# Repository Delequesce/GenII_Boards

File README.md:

## Rev 3 Changes

### Pi Interface and Power Board
1) ~~Set 4 LSBs of each color going into the RGB interface HIGH. This still allows for 4096 possible colors but frees up 12 total GPIOs.~~
2) ~~Replaced source switching circuitry with a source selector IC (LTC4412)~~. ~~Also implemented circuitry to enable the STM32 to shutdown and wakeup the Pi with the power button for better power management.~~ 
3) ~~Replaced the Pi Zero W with a Pi Zero 2 W.~~
4) ~~Added I2C RESET pin for enabling the capacitive touch screen~~
5) ~~Moved the FPC connector to the Measurement Board to the top of the board to ease assembly.~~ 
6) ~~Moved the RGB and I2C connectors to the screen closer to the edge (or top with flipped connections) to ease assembly.~~ 
7) ~~Fixed wiring issues for Vdd and Vcc out to the Measurement Board.~~
8) ~~Increased the size of the mounting holes for the battery cables to ease connection. (0.65 mm diameter for 22 AWG)~~
9) ~~Generally improved power routing~~
10) ~~Improved PWM backlight enable routing for better fidelity.~~
11) ~~Specced out smaller battery connectors to ease assembly and reduce size. (22 AWG, Amazon)~~
12) ~~Moved the Vdd Main LDO to the Measurement Board~~
13) ~~Added a fuse to the TPS2400 circuit and also a fuse after the source selector.~~
14) ~~Added a small board meant to be separated for interfacing the pushbutton reset switch with the rest of the circuit.~~

### Measurement Board
1) ~~Fixed PWM Heater signal routing~~ 
2) ~~Flipped FPC connector to Pi Board to top of board to ease assembly. Checked wiring against the Pi board.~~
3) ~~Moved Vdd Main LDO from Pi Board.~~ 
4) ~~Added external interrupt pin and Vcc controller output pin to interface with external pushbutton board. Needed to add 50 mils (1.27 mm) to board length.~~
5) ~~Changed the ADR4530 to the MAX6070, a cheaper buffered reference requiring fewer parts.~~

### Heater Board
1) ~~Reduced the size of vias and made more of them for better heating and lower losses. ~~
2) Moved the thermistors slightly farther from the center to improve temperature tracking. Alternately just reduced the size of the heating area to improve tracking without separating the thermistors from the chip. (Maybe)

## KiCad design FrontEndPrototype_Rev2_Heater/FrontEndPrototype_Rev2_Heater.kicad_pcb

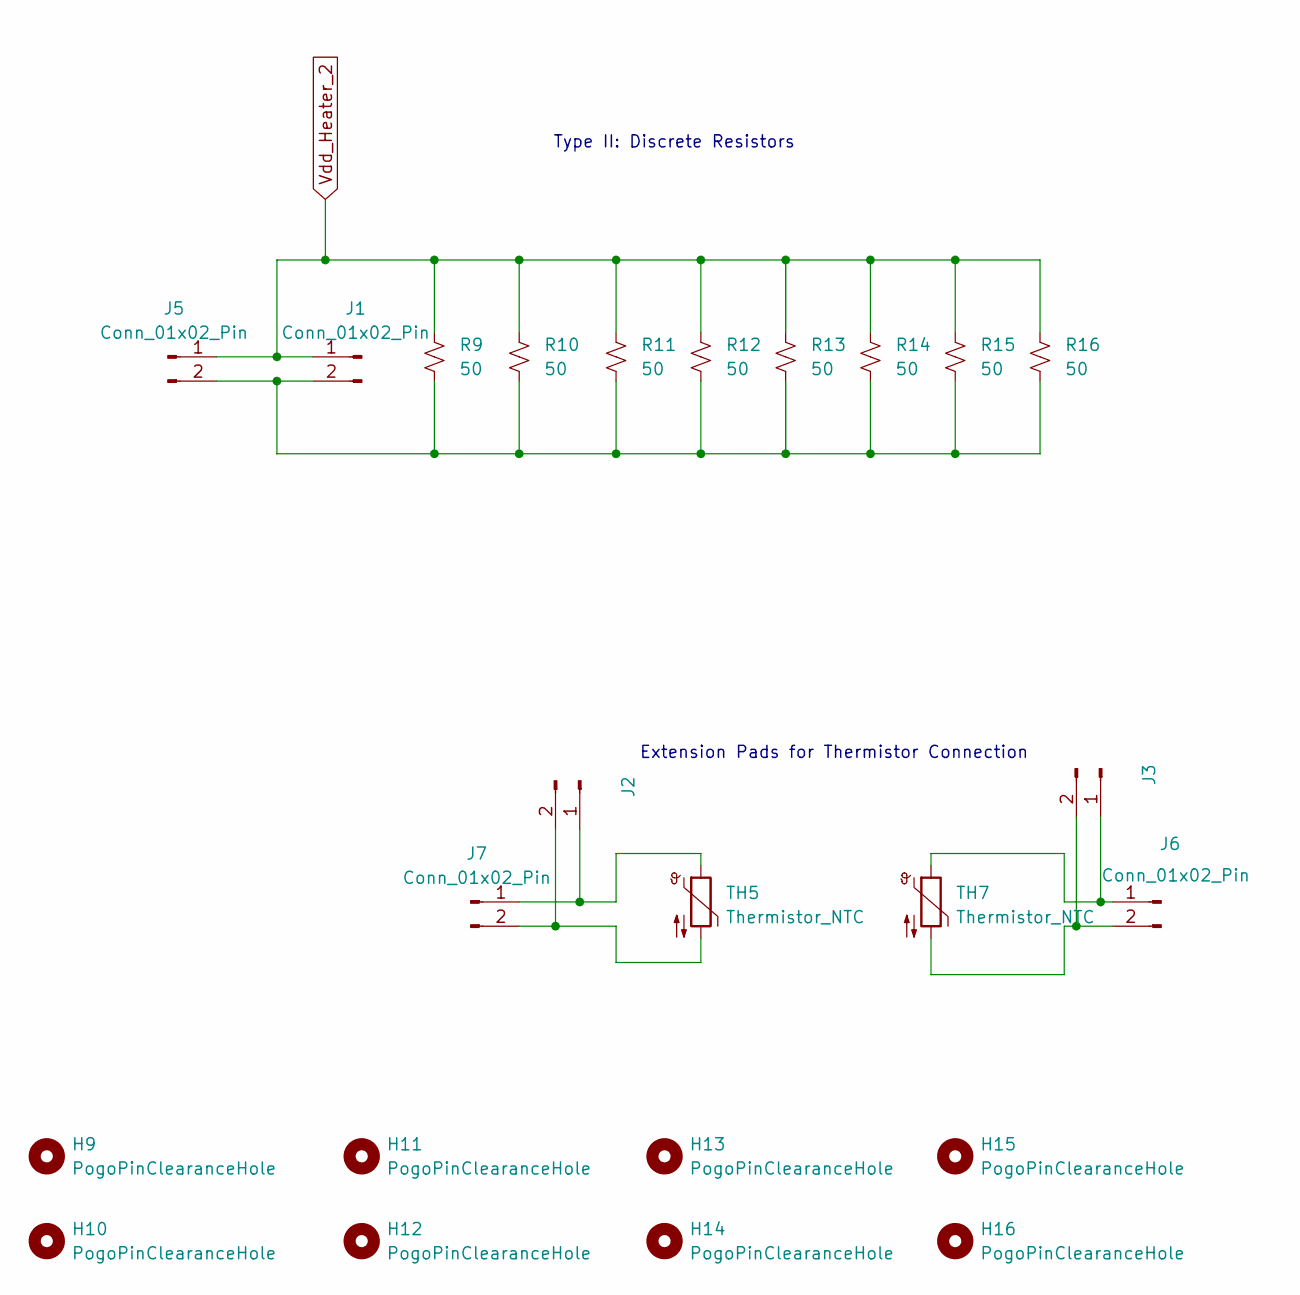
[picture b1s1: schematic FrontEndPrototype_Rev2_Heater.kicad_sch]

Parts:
H9, H10, H11, H12, H13, H14, H15, H16: PogoPinClearanceHole; PogoClearanceHole
J1, J5, J6, J7: Conn_01x02_Pin; Samtec_Pin_Socket_SS_102_G_2
J2, J3: Conn_01x02_Pin; Thermistor_ExtensionPad
R9, R10, R11, R12, R13, R14, R15, R16: 50; R_2010_5025Metric_Pad1.40x2.65mm_HandSolder
TH5, TH7: Thermistor_NTC; R_0603_1608Metric_Pad0.98x0.95mm_HandSolder

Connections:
unnamed: J1.2, J5.2, R9.1, R10.1, R11.1, R12.1, R13.1, R14.1, R15.1, R16.1
unnamed: J2.1, J7.1, TH5.1
unnamed: J2.2, J7.2, TH5.2
unnamed: J3.1, J6.1, TH7.1
unnamed: J3.2, J6.2, TH7.2
Vdd_Heater_2: J1.1, J5.1, R9.2, R10.2, R11.2, R12.2, R13.2, R14.2, R15.2, R16.2

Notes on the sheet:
Extension Pads for Thermistor Connection
Type II: Discrete Resistors

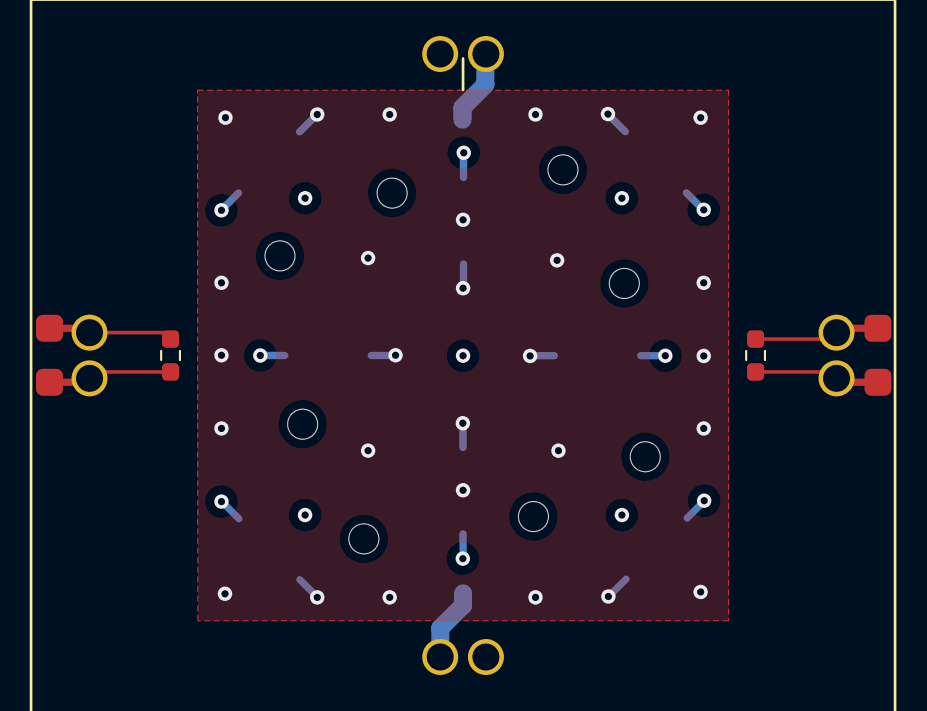
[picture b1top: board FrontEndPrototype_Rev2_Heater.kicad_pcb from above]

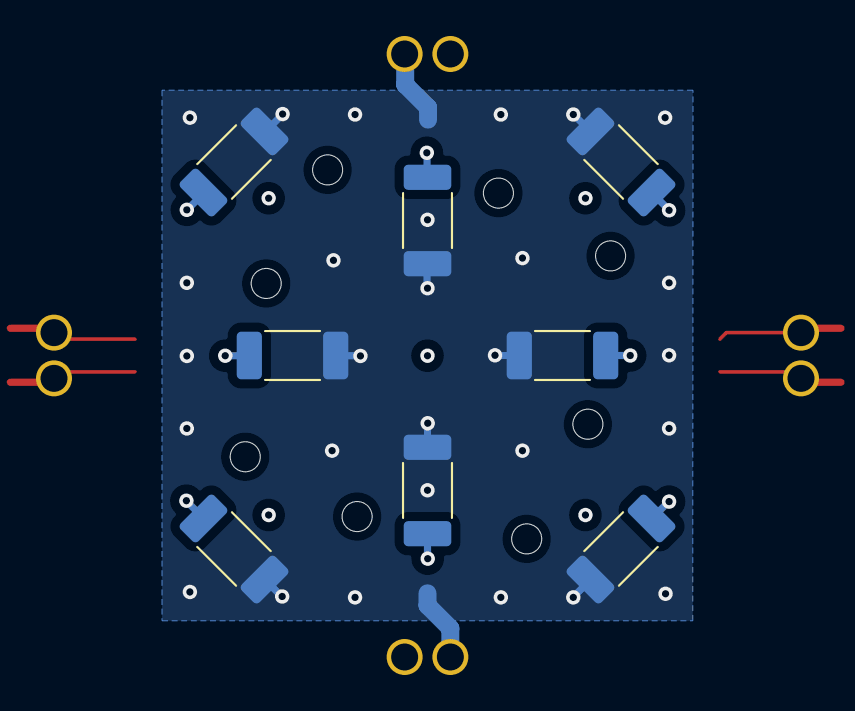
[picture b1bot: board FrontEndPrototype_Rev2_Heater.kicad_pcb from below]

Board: 4 copper layers, 24 parts (8 on the bottom side), 6 nets.

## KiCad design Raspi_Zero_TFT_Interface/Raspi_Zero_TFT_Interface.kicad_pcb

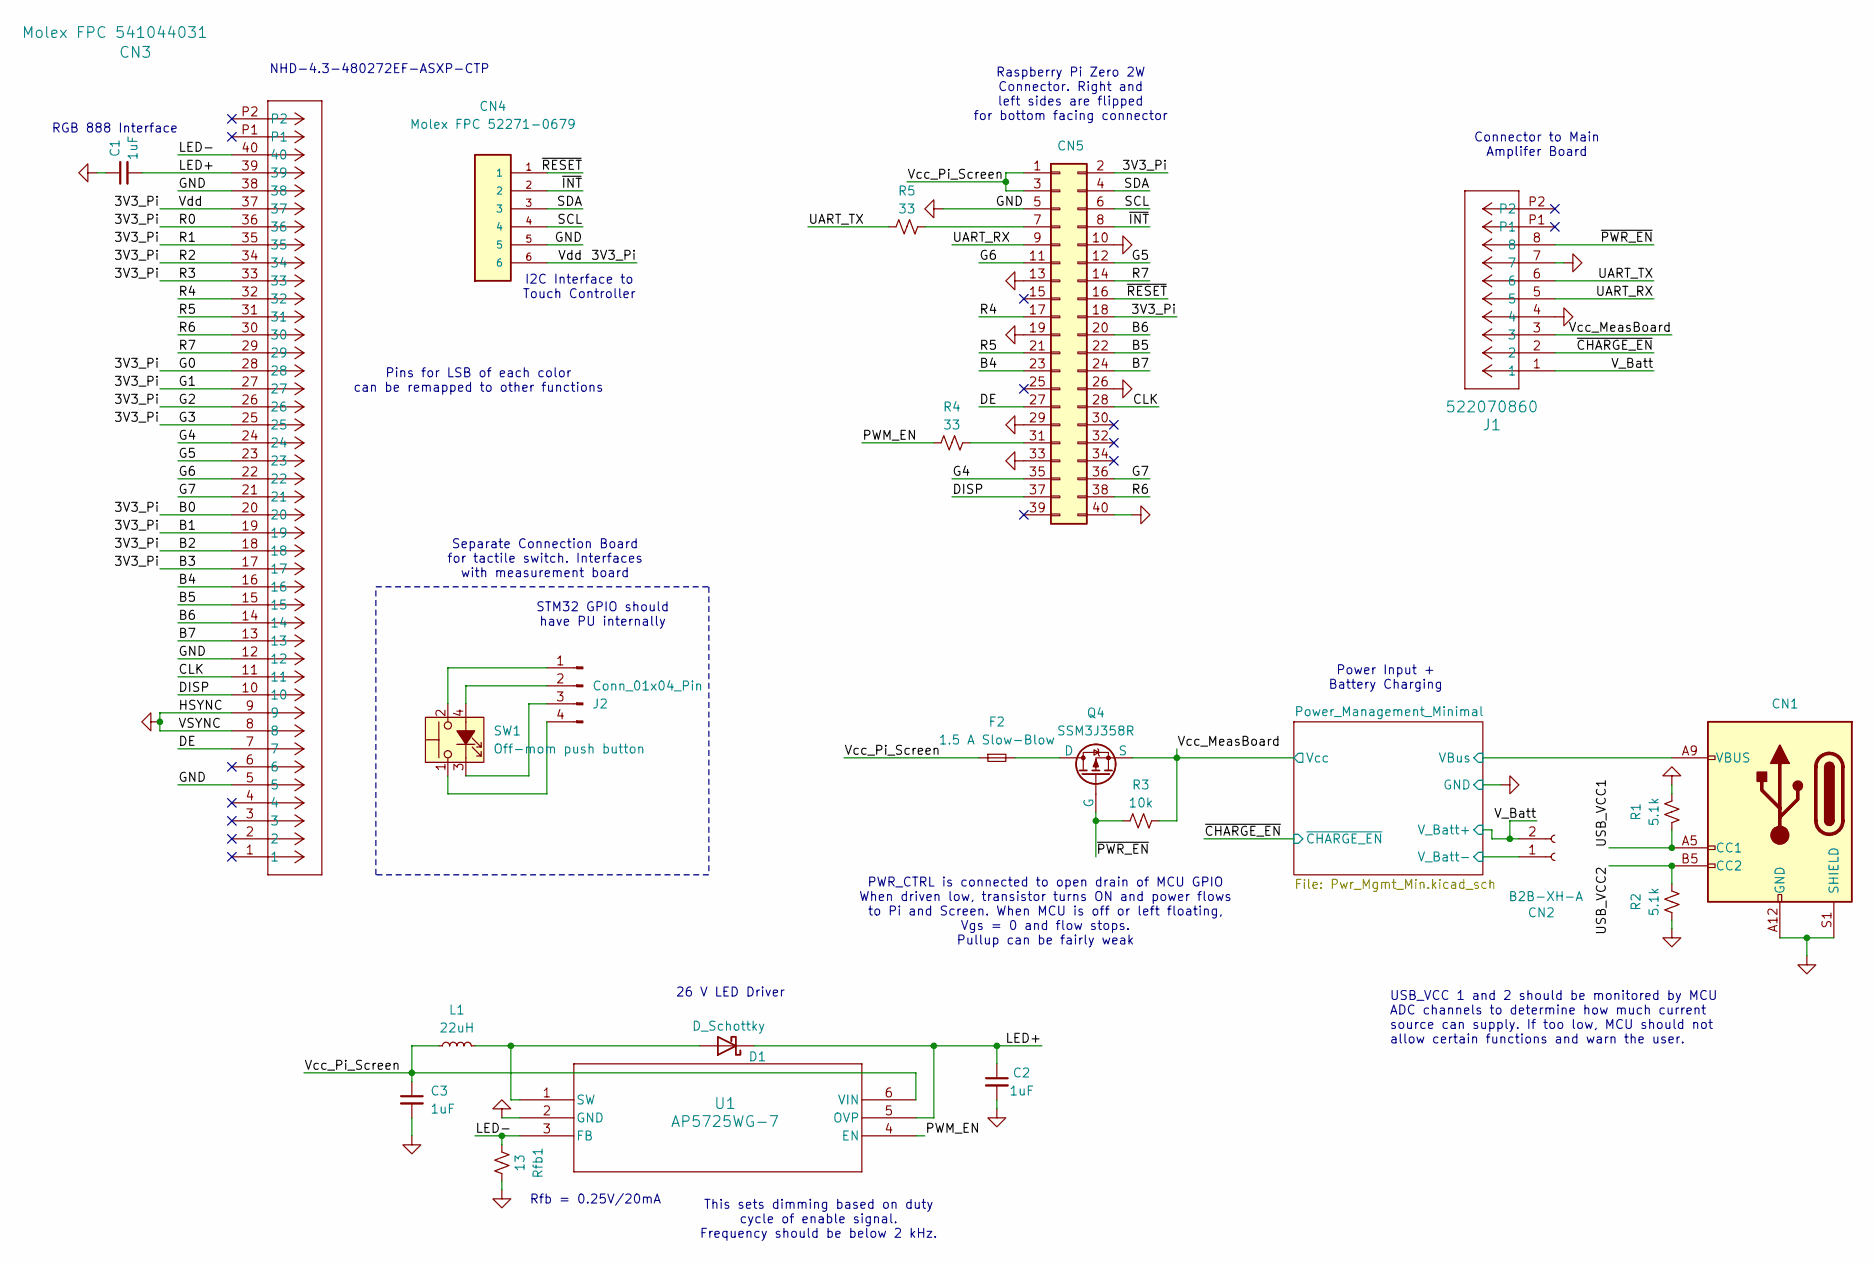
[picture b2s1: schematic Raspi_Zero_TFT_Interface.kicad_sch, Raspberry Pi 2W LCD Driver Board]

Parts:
C1, C2, C3: 1uF; C_0603_1608Metric_Pad1.08x0.95mm_HandSolder
CN1: USB_C_Receptacle_PowerOnly_6P; USB_C_Receptacle_GCT_USB4125-xx-x_6P_TopMnt_Horizontal
CN2: B2B-XH-A; JST_XH_B2B-XH-A_1x02_P2.50mm_Vertical
CN3: Molex FPC 541044031; CON_541044031_MOL
CN4: Molex FPC 52271-0679; MOLEX_52271-0679
CN5: Conn_02x20_Odd_Even; PinHeader_2x20_P2.54mm_Vertical
D1: D_Schottky; D_SOD-523
F2: 1.5 A Slow-Blow; Fuse_0603_1608Metric
J1: 522070860; CON_522070860_MOL
J2: Conn_01x04_Pin; PinHeader_1x04_P2.54mm_Vertical
L1: 22uH; L_0805_2012Metric_Pad1.15x1.40mm_HandSolder
Q4: SSM3J358R; SOT-23-3
R1, R2: 5.1k; R_0603_1608Metric_Pad0.98x0.95mm_HandSolder
R3: 10k; R_0603_1608Metric_Pad0.98x0.95mm_HandSolder
R4, R5: 33; R_0603_1608Metric_Pad0.98x0.95mm_HandSolder
Rfb1: 13; R_0603_1608Metric_Pad0.98x0.95mm_HandSolder
SW1: Off-mom push button; TL1240_LED_Switch
U1: AP5725WG-7; SOT-23-6_Handsoldering

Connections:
/3V3_Pi: CN3.17, CN3.18, CN3.19, CN3.20, CN3.25, CN3.26, CN3.27, CN3.28, CN3.33, CN3.34, CN3.35, CN3.36, CN3.37, CN4.6, CN5.2, CN5.18
/B4: CN3.16, CN5.23
/B5: CN3.15, CN5.22
/B6: CN3.14, CN5.20
/B7: CN3.13, CN5.24
/CLK: CN3.11, CN5.28
/DE: CN3.7, CN5.27
/DISP: CN3.10, CN5.37
/G4: CN3.24, CN5.35
/G5: CN3.23, CN5.12
/G6: CN3.22, CN5.11
/G7: CN3.21, CN5.36
/LED+: C1.2, C2.1, CN3.39, D1.1 (K), U1.5 (OVP)
/LED-: CN3.40, Rfb1.2, U1.3 (FB)
/PWM_EN: R4.1, U1.4 (EN)
/Power_Management_Minimal/VBus: CN1.A9 (VBUS), CN1.B9 (VBUS); also elsewhere on the board
/R4: CN3.32, CN5.17
/R5: CN3.31, CN5.21
/R6: CN3.30, CN5.38
/R7: CN3.29, CN5.14
/SCL: CN4.4, CN5.6
/SDA: CN4.3, CN5.4
/UART_RX: CN5.9, J1.5
/UART_TX: J1.6, R5.1
/USB_VCC1: CN1.A5 (CC1), R1.2
/USB_VCC2: CN1.B5 (CC2), R2.2
/V_Batt: CN2.2, J1.1; also elsewhere on the board
/Vcc_MeasBoard: J1.3, Q4.2 (S), R3.2; also elsewhere on the board
/Vcc_Pi_Screen: C3.1, CN5.1, CN5.3, F2.1, L1.1, U1.6 (VIN)
/~CHARGE_EN: J1.2; also elsewhere on the board
/~INT: CN4.2, CN5.8
/~PWR_EN: J1.8, Q4.1 (G), R3.1
/~RESET: CN4.1, CN5.16
GND: C1.1, C2.2, C3.2, CN1.A12 (GND), CN1.B12 (GND), CN1.S1 (SHIELD), CN2.1, CN3.5, CN3.8, CN3.9, CN3.12, CN3.38, CN4.5, CN5.5, CN5.10, CN5.13, CN5.19, CN5.26, CN5.29, CN5.33, CN5.40, J1.4, J1.7, R1.1, R2.1, Rfb1.1, U1.2 (GND); also elsewhere on the board
unnamed: CN5.7, R5.2
unnamed: CN5.31, R4.2
unnamed: D1.2 (A), L1.2, U1.1 (SW)
unnamed: J2.1, SW1.2
unnamed: J2.2, SW1.4 (A)
unnamed: J2.3, SW1.3 (K)
unnamed: J2.4, SW1.1
unnamed: F2.2, Q4.3 (D)

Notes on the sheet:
I2C Interface to Touch Controller
RGB 888 Interface
STM32 GPIO should have PU internally
Pins for LSB of each color can be remapped to other functions
NHD-4.3-480272EF-ASXP-CTP
USB_VCC 1 and 2 should be monitored by MCU ADC channels to determine how much current source can supply. If too low, MCU should not allow certain functions and warn the user.
Separate Connection Board for tactile switch. Interfaces with measurement board
Raspberry Pi Zero 2W Connector. Right and left sides are flipped for bottom facing connector
PWR_CTRL is connected to open drain of MCU GPIO When driven low, transistor turns ON and power flows to Pi and Screen. When MCU is off or left floating, Vgs = 0 and flow stops. Pullup can be fairly weak
This sets dimming based on duty cycle of enable signal. Frequency should be below 2 kHz.
26 V LED Driver
Connector to Main Amplifer Board
Rfb = 0.25V/20mA
Power Input + Battery Charging

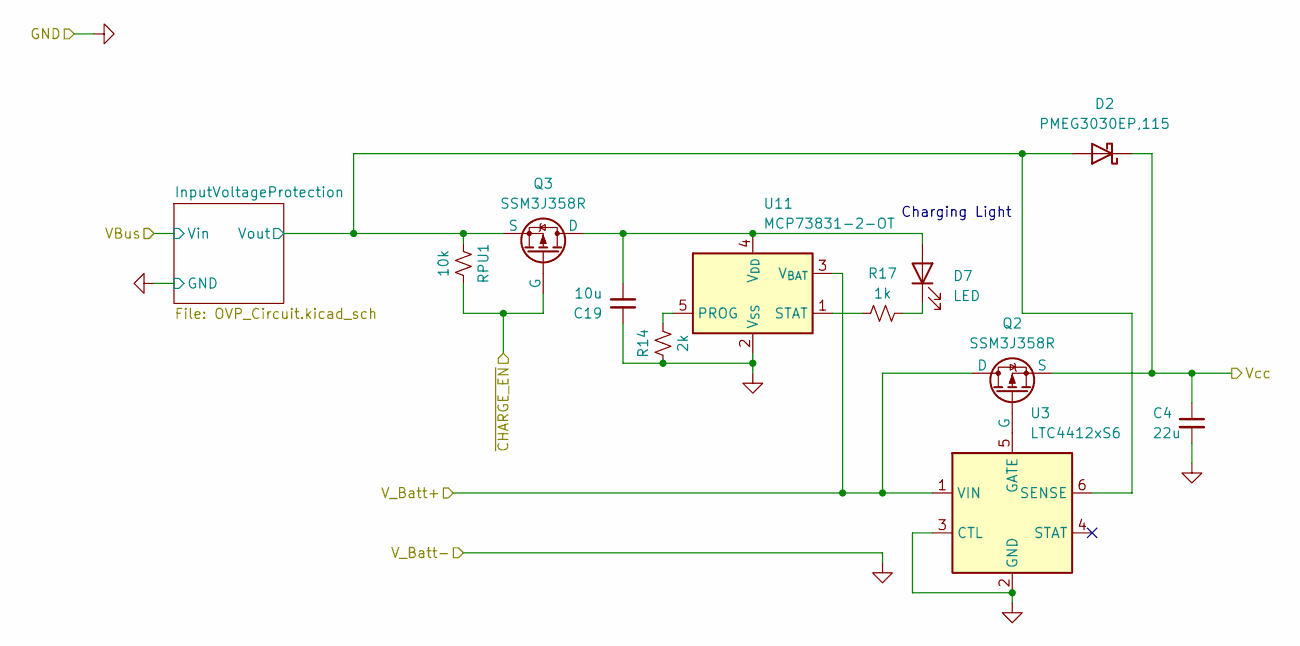
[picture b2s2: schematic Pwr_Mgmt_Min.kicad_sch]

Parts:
C4: 22u; C_0603_1608Metric_Pad1.08x0.95mm_HandSolder
C19: 10u; C_0603_1608Metric_Pad1.08x0.95mm_HandSolder
D2: PMEG3030EP,115; D_SOD-128
D7: LED; D_T-1_P2.54mm_Vertical_AnodeUp
Q2, Q3: SSM3J358R; SOT-23-3
R14: 2k; R_0603_1608Metric_Pad0.98x0.95mm_HandSolder
R17: 1k; R_0603_1608Metric_Pad0.98x0.95mm_HandSolder
RPU1: 10k; R_0603_1608Metric_Pad0.98x0.95mm_HandSolder
U3: LTC4412xS6; TSOT-23-6
U11: MCP73831-2-OT; SOT-23-5

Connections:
/Power_Management_Minimal/InputVoltageProtection/Vout: D2.2 (A), Q3.2 (S), RPU1.1, U3.6 (SENSE); also elsewhere on the board
/V_Batt: Q2.3 (D), U3.1 (VIN), U11.3 (V_{BAT}); also elsewhere on the board
/Vcc_MeasBoard: C4.1, D2.1 (K), Q2.2 (S); also elsewhere on the board
/~CHARGE_EN: Q3.1 (G), RPU1.2; also elsewhere on the board
GND: C4.2, C19.1, R14.1, U3.2 (GND), U3.3 (CTL), U11.2 (V_{SS}); also elsewhere on the board
unnamed: C19.2, D7.2 (A), Q3.3 (D), U11.4 (V_{DD})
unnamed: D7.1 (K), R17.2
unnamed: Q2.1 (G), U3.5 (GATE)
unnamed: R14.2, U11.5 (PROG)
unnamed: R17.1, U11.1 (STAT)

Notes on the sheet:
Charging Light

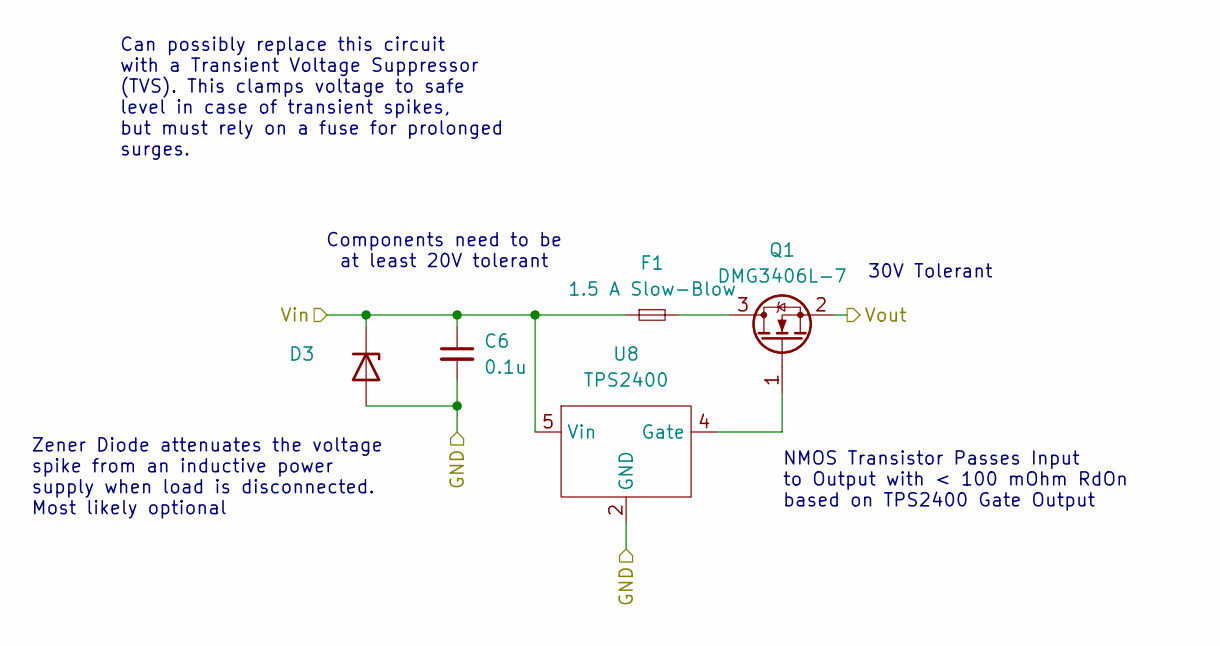
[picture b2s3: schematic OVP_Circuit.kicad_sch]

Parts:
C6: 0.1u; C_0603_1608Metric_Pad1.08x0.95mm_HandSolder
D3: NC; D_SOD-123
F1: 1.5 A Slow-Blow; Fuse_0603_1608Metric
Q1: DMG3406L-7; SOT-23-3
U8: TPS2400; SOT-23-5_HandSoldering

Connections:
/Power_Management_Minimal/InputVoltageProtection/Vout: Q1.2 (S); also elsewhere on the board
/Power_Management_Minimal/VBus: C6.1, D3.1 (K), F1.1, U8.5 (Vin); also elsewhere on the board
GND: C6.2, D3.2 (A), U8.2 (GND); also elsewhere on the board
unnamed: F1.2, Q1.3 (D)
unnamed: Q1.1 (G), U8.4 (Gate)

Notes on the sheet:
30V Tolerant
NMOS Transistor Passes Input to Output with < 100 mOhm RdOn based on TPS2400 Gate Output
Components need to be at least 20V tolerant
Zener Diode attenuates the voltage spike from an inductive power supply when load is disconnected. Most likely optional
Can possibly replace this circuit with a Transient Voltage Suppressor (TVS). This clamps voltage to safe level in case of transient spikes, but must rely on a fuse for prolonged surges.

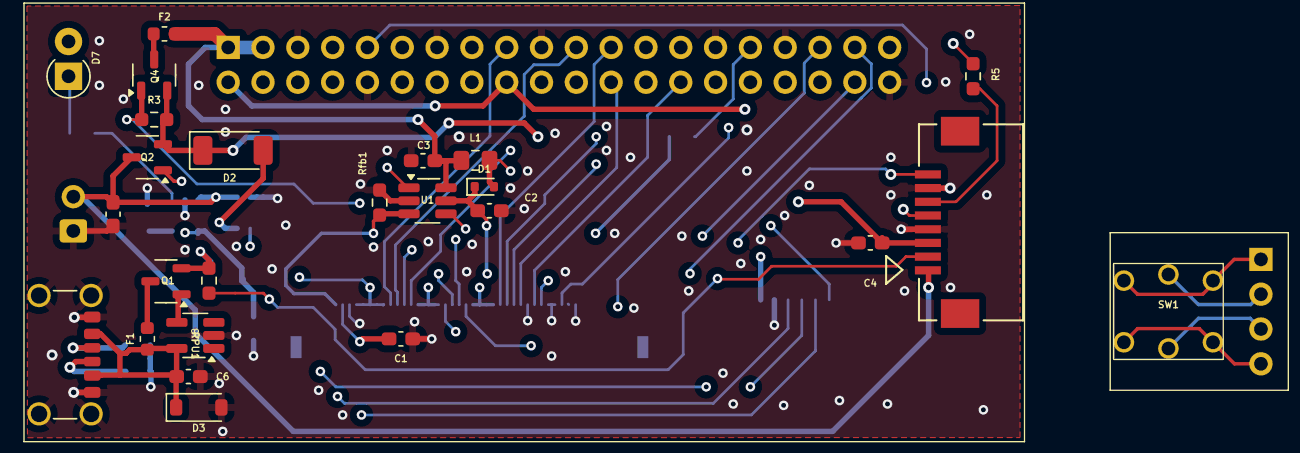
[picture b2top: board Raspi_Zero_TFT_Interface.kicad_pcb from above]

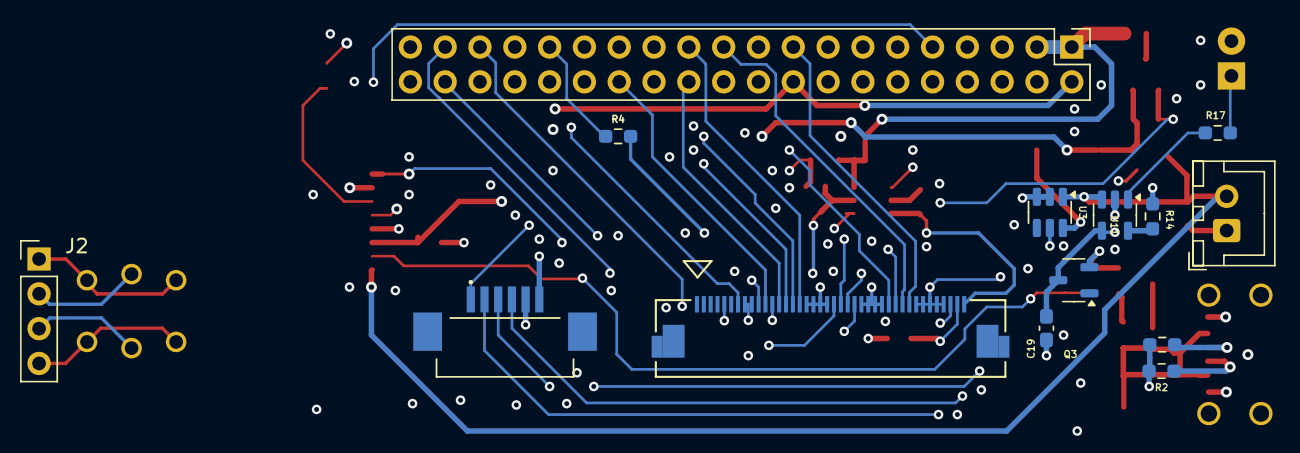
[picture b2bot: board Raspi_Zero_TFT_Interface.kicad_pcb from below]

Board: 4 copper layers, 39 parts (14 on the bottom side), 50 nets.

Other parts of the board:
C20: 10u; C_0603_1608Metric_Pad1.08x0.95mm_HandSolder

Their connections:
/V_Batt: C20.1; also elsewhere on the board
GND: C20.2; also elsewhere on the board

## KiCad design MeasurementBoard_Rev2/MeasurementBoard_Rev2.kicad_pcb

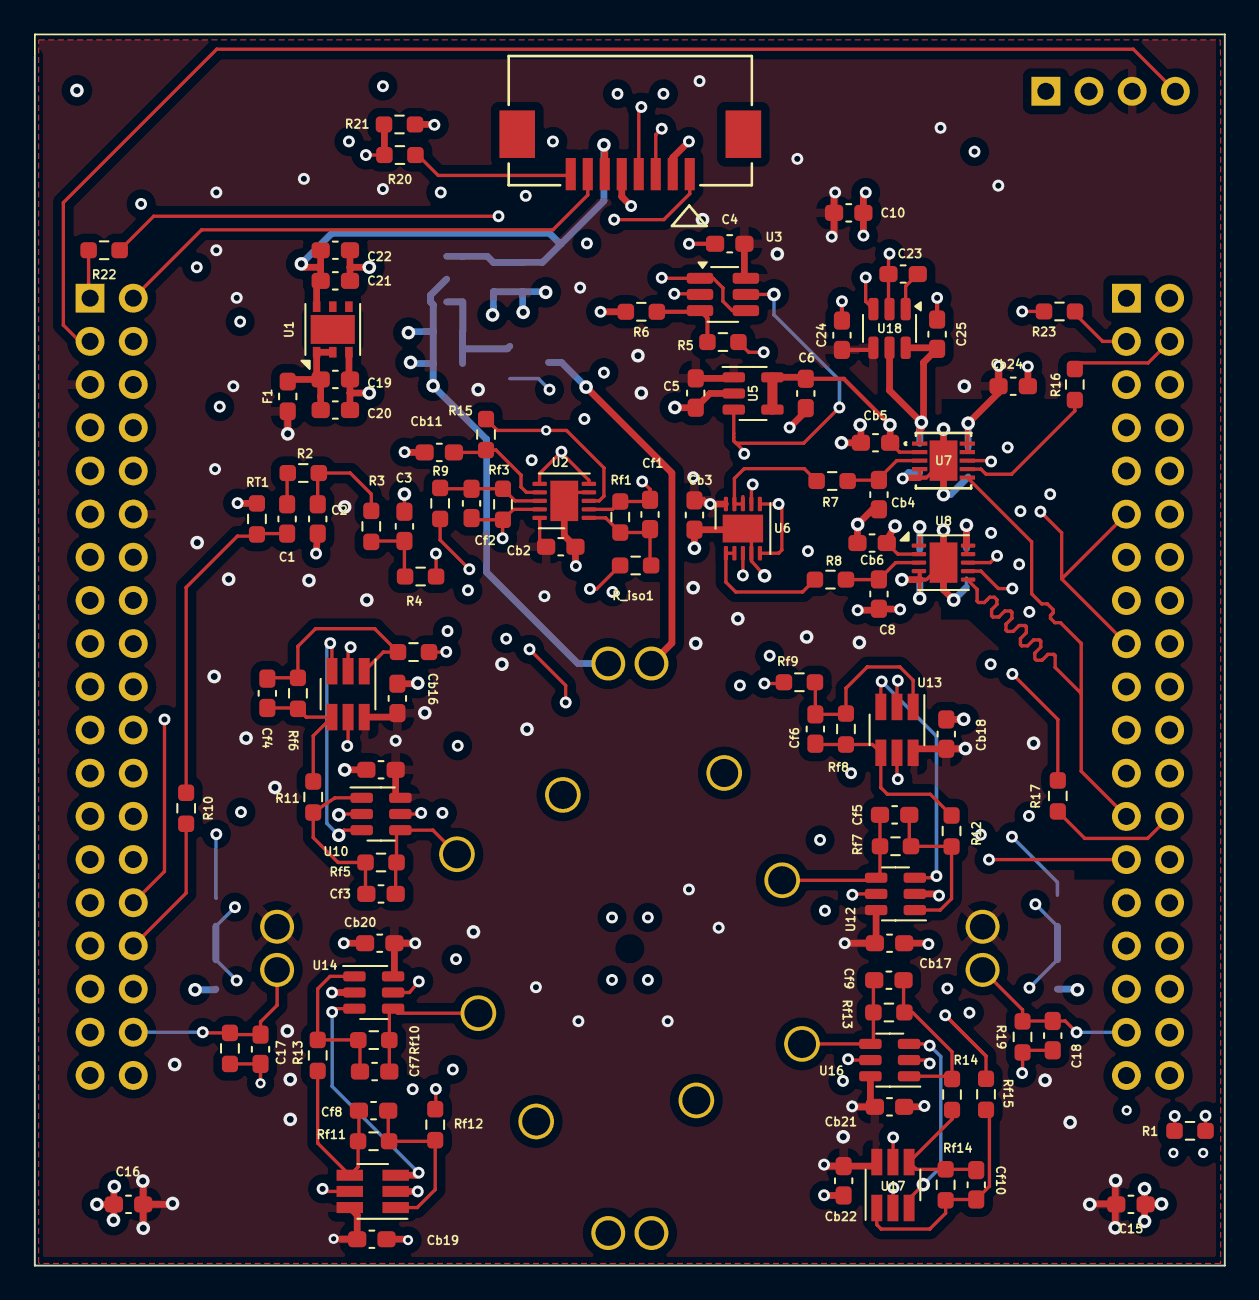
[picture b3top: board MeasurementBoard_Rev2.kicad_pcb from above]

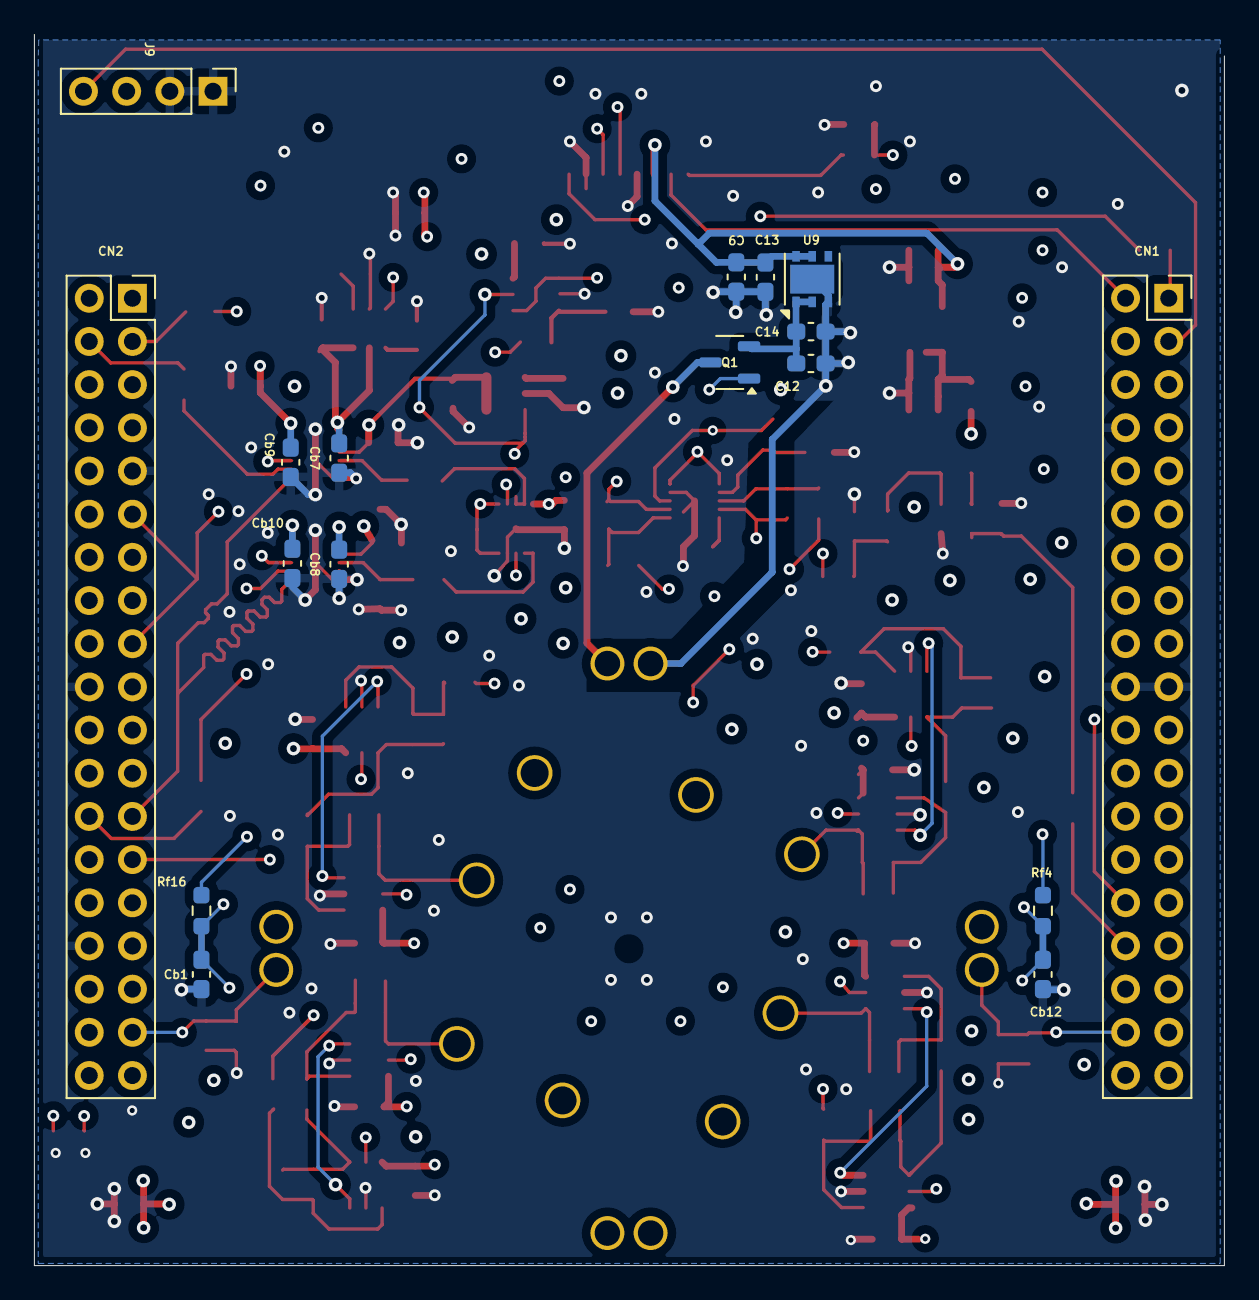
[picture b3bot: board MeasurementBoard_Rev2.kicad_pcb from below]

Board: 4 copper layers, 70.0 x 72.4 mm, 130 parts (17 on the bottom side), 69 nets.

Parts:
C1: 100p; C_0603_1608Metric_Pad1.08x0.95mm_HandSolder
C2, C3: 47p; C_0603_1608Metric_Pad1.08x0.95mm_HandSolder
C4, C23, C24: 0.1uF; C_0603_1608Metric_Pad1.08x0.95mm_HandSolder
C5, C6, C17, C18: 10uF; C_0603_1608Metric_Pad1.08x0.95mm_HandSolder
C8: 220p; C_0603_1608Metric_Pad1.08x0.95mm_HandSolder
C9, C12, C20, C21: 1uF/XR5; C_0603_1608Metric_Pad1.08x0.95mm_HandSolder
C10: 22uF; C_0603_1608Metric_Pad1.08x0.95mm_HandSolder
C13, C14, C19, C22: 100n; C_0603_1608Metric_Pad1.08x0.95mm_HandSolder
C15, C16: 22u; C_0603_1608Metric_Pad1.08x0.95mm_HandSolder
C25: 1uF; C_0603_1608Metric_Pad1.08x0.95mm_HandSolder
CN1, CN2: Conn_02x19_Odd_Even; PinSocket_2x19_P2.54mm_Vertical
CN3: 522070860; CON_522070860_MOL
CN4, CN5, CN6, CN7: Conn_01x02_Pin; Samtec_Pin_Socket_SS_102_G_2
Cb1, Cb7, Cb8, Cb12: 10u; C_0603_1608Metric_Pad1.08x0.95mm_HandSolder
Cb2, Cb3, Cb5, Cb6, Cb9, Cb10, Cb15, Cb16, Cb17, Cb18, Cb19, Cb20, Cb21, Cb22, Cb24: 0.1u; C_0603_1608Metric_Pad1.08x0.95mm_HandSolder
Cb4: 220p; C_0603_1608Metric_Pad1.08x0.95mm_HandSolder
Cb11: 1u; C_0603_1608Metric_Pad1.08x0.95mm_HandSolder
Cf1: 27p; C_0603_1608Metric_Pad1.08x0.95mm_HandSolder
Cf2, Cf4, Cf6, Cf8, Cf10: 1p; C_0603_1608Metric_Pad1.08x0.95mm_HandSolder
Cf3, Cf5, Cf7, Cf9: 200p; C_0603_1608Metric_Pad1.08x0.95mm_HandSolder
F1: 250mA Fast-Blow; Fuse_0603_1608Metric_Pad1.05x0.95mm_HandSolder
J1, J2, J3, J4, J5, J6, J7, J8: MIllMaxSpringConnector; MillMax_0914-2
J9: Connector to Power Switch; PinHeader_1x04_P2.54mm_Vertical
Q1: SSM3J358R; SOT-23-3
R1, R10, R16, R17, R22: 33; R_0603_1608Metric_Pad0.98x0.95mm_HandSolder
R2, R3, R5, R6, R20, R21: 10k; R_0603_1608Metric_Pad0.98x0.95mm_HandSolder
R4, R9, R11, R12, R13, R14, R15, R18, R19: 1k; R_0603_1608Metric_Pad0.98x0.95mm_HandSolder
R7, R8: 100; R_0603_1608Metric_Pad0.98x0.95mm_HandSolder
R23: 27k; R_0603_1608Metric_Pad0.98x0.95mm_HandSolder
RT1: NC; R_0603_1608Metric_Pad0.98x0.95mm_HandSolder
R_iso1: 10; R_0603_1608Metric_Pad0.98x0.95mm_HandSolder
Rf1: 1.5k; R_0603_1608Metric_Pad0.98x0.95mm_HandSolder
Rf3, Rf6, Rf8, Rf11, Rf14: 39k; R_0603_1608Metric_Pad0.98x0.95mm_HandSolder
Rf4, Rf16: 100; R_0603_1608Metric_Pad0.98x0.95mm_HandSolder
Rf5, Rf7, Rf10, Rf13: 50; R_0603_1608Metric_Pad0.98x0.95mm_HandSolder
Rf9, Rf12, Rf15: 10; R_0603_1608Metric_Pad0.98x0.95mm_HandSolder
Riso1: 10; R_0603_1608Metric_Pad0.98x0.95mm_HandSolder
U1, U9: LD39200_Fixed; DFN-6-1EP_3x3mm_P0.95mm_EP1.7x2.6mm
U2, U6: ADA4807-2ACP; LFCSP-WD-10-1EP_3x3mm_P0.5mm_EP1.64x2.38mm
U3, U11, U13, U15, U17: ADA4807-1; SOT-23-6_Handsoldering
U5: ADP7118-1.8; TSOT-23-5
U7: AD4002_LFSCP-10; CP_10_9_ADI
U8: AD4002_LFSCP-10; LFCSP-WD-10-1EP_3x3mm_P0.5mm_EP1.64x2.38mm
U10, U12, U14, U16: LTC6252; TSOT-23-6
U18: MAX6070BAUT30+T; SOT-23-6

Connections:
/ABBCore_Alt/TIA_1/V_MID: Cb12.2, Rf4.2, U10.3 (+), U11.3 (+), U14.3 (+), U15.3 (+)
/ABBCore_Alt/TIA_2/V_MID: Cb1.2, Rf16.2, U12.3 (+), U13.3 (+), U16.3 (+), U17.3 (+)
/ABBCore_Alt/V_Drive: J3.1, J4.1, J7.1, J8.1, R9.2, R_iso1.2
/ABBCore_Alt/V_Exc: Cf2.2, Rf3.2, U2.9, U6.7 (+)
/ABBCore_Alt/V_Resp: Rf9.2, Rf12.2, Rf15.2, Riso1.2, U6.3 (+)
/Heater_Interface/Heater+: CN7.2, Q1.3 (D)
/MCU Connections/PA1: CN1.32, R10.1
/MCU Connections/PB4: CN2.4, R16.2
/MCU Connections/PB6: CN2.34, R1.1
/MCU Connections/PB8: CN2.3, R23.1
/MCU Connections/PB11: CN1.1, R22.2
/MCU Connections/PB15: CN2.26, R17.1
/MCU Connections/PC1: CN1.30, R20.2, R21.1
ADC_VREF: C25.2, Cb7.2, Cb8.2, R5.1, U7.1 (REF), U8.1 (REF), U18.5 (OUTS), U18.6 (OUTF)
CCOut_1: Cf3.1, J6.1, Rf5.1, U10.4 (-)
CCOut_2: Cf5.1, J5.1, Rf7.1, U12.4 (-)
CCOut_3: Cf7.1, J2.1, Rf10.1, U14.4 (-)
CCOut_4: Cf9.1, J1.1, Rf13.1, U16.4 (-)
CNV: CN2.25, U7.6 (CNV), U8.6 (CNV)
DataOut1: R17.2, U8.7 (SDO)
Dataout0: R16.1, U7.7 (SDO)
GND: C2.2, C3.2, C4.1, C5.2, C6.2, C8.1, C9.1, C10.1, C12.2, C13.2, C14.2, C15.1, C16.1, C17.2, C18.1, C19.2, C20.2, C21.1, C22.2, C23.1, C24.1, C25.1, CN1.8, CN1.19, CN1.20, CN2.9, CN2.20, CN2.32, CN3.2, CN3.5, CN7.1, Cb1.1, Cb2.1, Cb3.2, Cb4.1, Cb5.2, Cb6.2, Cb7.1, Cb8.1, Cb9.1, Cb10.1, Cb11.1, Cb12.1, Cb15.1, Cb16.1, Cb17.1, Cb18.1, Cb19.1, Cb20.1, Cb21.1, Cb22.1, Cb24.1, J9.1, J9.2, R6.2, R18.1, R19.1, R21.2, RT1.1, U1.3 (GND), U1.7, U2.4 (V-), U2.11 (EPAD), U3.2 (V-), U5.2 (GND), U6.4 (V-), U6.11 (EPAD), U7.4 (IN-), U7.5 (GND), U7.11 (Pad), U8.4 (IN-), U8.5 (GND), U8.11 (Pad), U9.3 (GND), U9.7, U10.2 (V-), U11.2 (V-), U12.2 (V-), U13.2 (V-), U14.2 (V-), U15.2 (V-), U16.2 (V-), U17.2 (V-), U18.2 (GND)
Heater_PWM: Q1.1 (G), R23.2
MCU_SCK: CN2.11, CN2.17, U7.8 (SCK), U8.8 (SCK)
unnamed: C1.1, R2.1
unnamed: C2.1, R2.2, R3.1
unnamed: C3.1, R3.2, R4.1
unnamed: Cf1.1, R_iso1.1, Rf1.1, U2.1
unnamed: Cf3.2, R11.2, Rf5.2, U10.1
unnamed: Cf4.2, Rf6.2, Riso1.1, U11.1
unnamed: Cf5.2, R12.2, Rf7.2, U12.1
unnamed: Cf6.2, Rf8.2, Rf9.1, U13.1
unnamed: Cf7.2, R13.2, Rf10.2, U14.1
unnamed: Cf8.2, Rf11.2, Rf12.1, U15.1
unnamed: Cf9.2, R14.2, Rf13.2, U16.1
unnamed: Cf10.2, Rf14.2, Rf15.1, U17.1
unnamed: C12.1, C14.1, Q1.2 (S), U9.1 (Vout), U9.2 (ADJ/SENSE)
unnamed: C19.1, C20.1, F1.2, U1.1 (Vout), U1.2 (ADJ/SENSE)
unnamed: Cf1.2, R4.2, Rf1.2, U2.2 (-)
unnamed: Cb11.2, R15.2, U2.7 (+)
unnamed: Cf2.1, R9.1, Rf3.1, U2.8 (-)
unnamed: R5.2, R6.1, U3.3 (+)
unnamed: R8.2, U6.1, U6.2 (-)
unnamed: R7.2, U6.8 (-), U6.9
unnamed: Cb4.2, R7.1, U7.3 (IN+)
unnamed: C8.2, R8.1, U8.3 (IN+)
unnamed: Cf4.1, R11.1, Rf6.1, U11.4 (-)
unnamed: Cf6.1, R12.1, Rf8.1, U13.4 (-)
unnamed: Cf8.1, R13.1, Rf11.1, U15.4 (-)
unnamed: Cf10.1, R14.1, Rf14.1, U17.4 (-)
unnamed: C23.2, U18.1 (FILTER)
UART_RX: CN2.6, CN3.3
UART_TX: CN3.4, R1.2
V_Batt: CN3.8, R20.1
V_MID: R15.1, Rf4.1, Rf16.1, U2.3 (+), U3.1, U3.4 (-)
V_SIG: C1.2, R10.2, RT1.2
Vcc: C9.2, C13.1, C21.2, C22.1, CN3.6, U1.5 (EN), U1.6 (Vin), U9.5 (EN), U9.6 (Vin)
Vdd_ADC: C6.1, Cb5.1, Cb6.1, U5.4 (SENSE/ADJ), U5.5 (VOUT), U7.2 (Vdd), U8.2 (Vdd)
Vdd_Main: C4.2, C5.1, C10.2, C15.2, C16.2, C24.2, CN1.5, CN1.12, CN4.1, CN5.1, Cb2.2, Cb3.1, Cb9.2, Cb10.2, Cb15.2, Cb16.2, Cb17.2, Cb18.2, Cb19.2, Cb20.2, Cb21.2, Cb22.2, Cb24.2, F1.1, J9.3, U2.10 (V+), U3.6 (V+), U5.1 (VIN), U6.10 (V+), U7.9 (SDI), U7.10 (VIO), U8.9 (SDI), U8.10 (VIO), U10.6 (V+), U11.6 (V+), U12.6 (V+), U13.6 (V+), U14.6 (V+), U15.6 (V+), U16.6 (V+), U17.6 (V+), U18.4 (VIN)
Vth_1: C17.1, CN1.36, CN4.2, R18.2
Vth_2: C18.2, CN2.35, CN5.2, R19.2
~ADC1_SHDN: CN2.1, U2.5 (~DISABLE1), U2.6 (~DISABLE2), U3.5 (~DISABLE), U5.3 (EN), U6.5 (~DISABLE1), U6.6 (~DISABLE2), U18.3 (EN)
~CHARGE_EN: CN1.2, CN3.7
~PWR_EN: CN3.1, R22.1
~Power_Switch_INT: CN1.3, J9.4
~TIA1_SHDN: CN1.28, U10.5 (~SHDN), U11.5 (~DISABLE)
~TIA2_SHDN: CN2.27, U12.5 (~SHDN), U13.5 (~DISABLE)
~TIA3_SHDN: CN1.34, U14.5 (~SHDN), U15.5 (~DISABLE)
~TIA4_SHDN: CN2.33, U16.5 (~SHDN), U17.5 (~DISABLE)

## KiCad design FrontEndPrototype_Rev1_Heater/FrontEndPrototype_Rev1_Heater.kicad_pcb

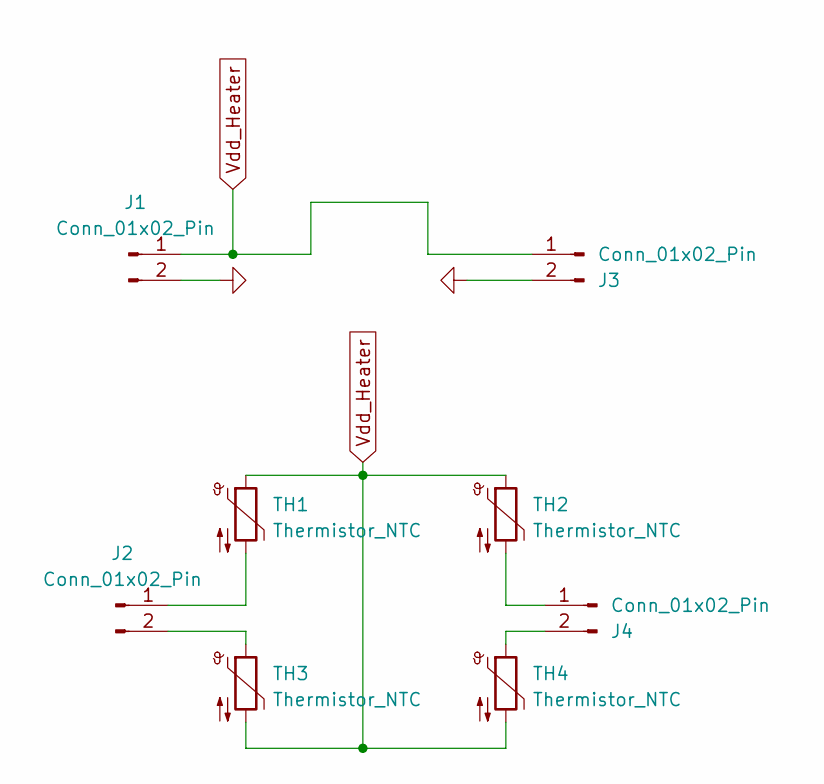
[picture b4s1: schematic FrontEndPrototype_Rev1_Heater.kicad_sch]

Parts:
J1, J2, J3, J4: Conn_01x02_Pin; Samtec_Pin_Socket_SS_102_G_2
TH1, TH2, TH3, TH4: Thermistor_NTC; R_0603_1608Metric_Pad0.98x0.95mm_HandSolder

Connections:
GND: J1.2, J3.2
unnamed: J2.1, TH1.2
unnamed: J2.2, TH3.1
unnamed: J4.1, TH2.2
unnamed: J4.2, TH4.1
Vdd_Heater: J1.1, J3.1, TH1.1, TH2.1, TH3.2, TH4.2

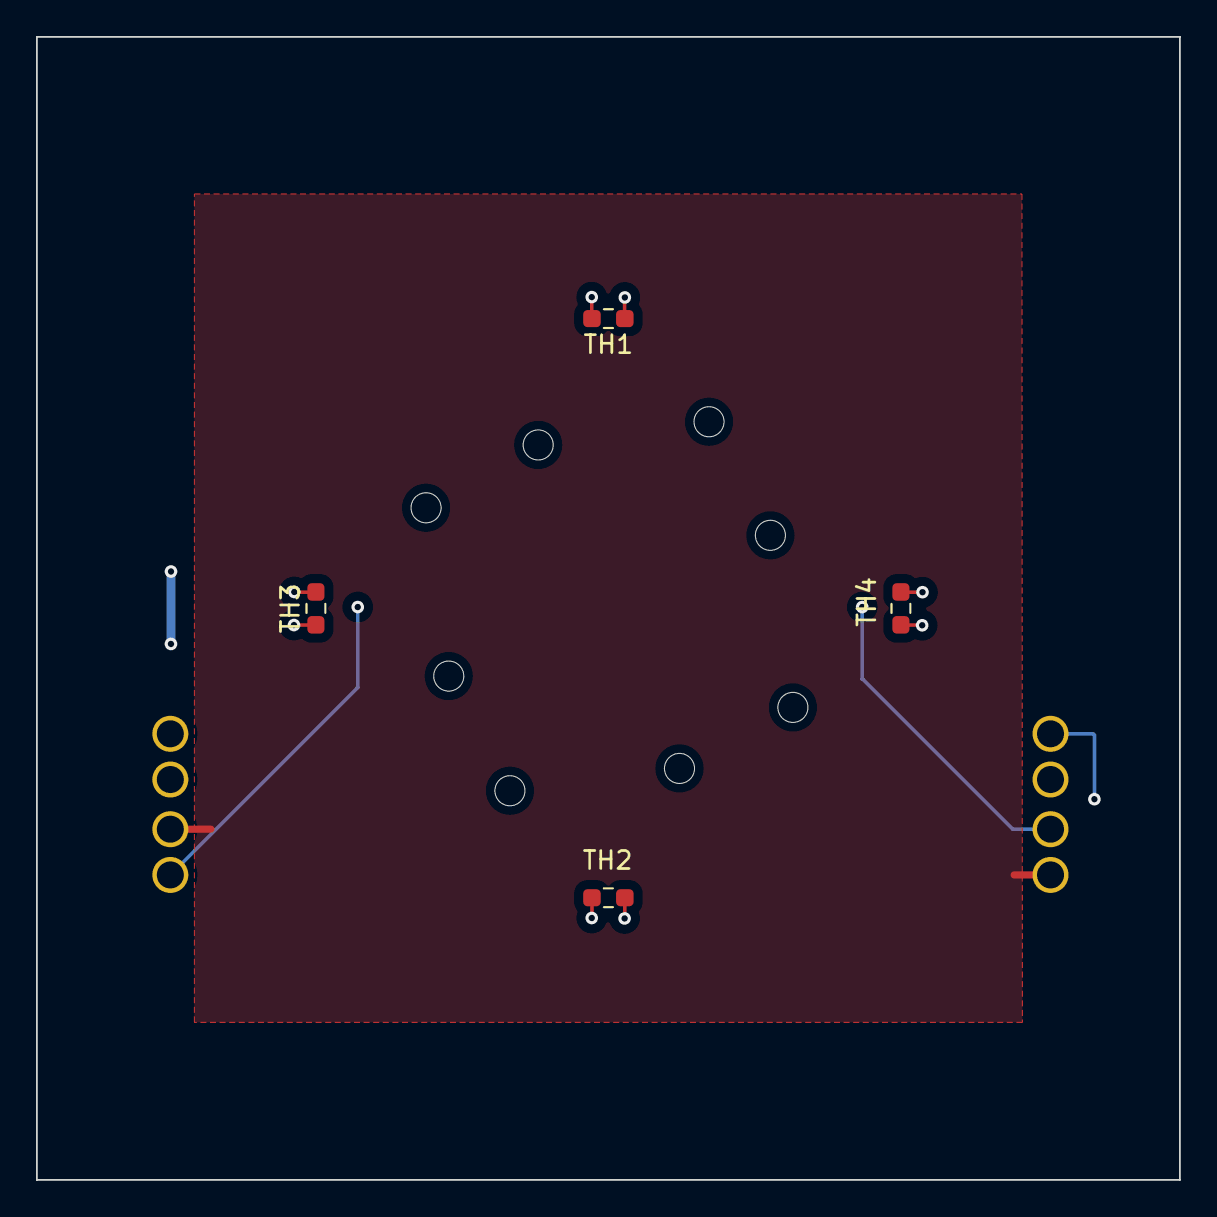
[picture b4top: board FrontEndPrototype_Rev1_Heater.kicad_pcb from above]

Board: 4 copper layers, 63.5 x 63.5 mm, 8 parts (0 on the bottom side), 6 nets.
